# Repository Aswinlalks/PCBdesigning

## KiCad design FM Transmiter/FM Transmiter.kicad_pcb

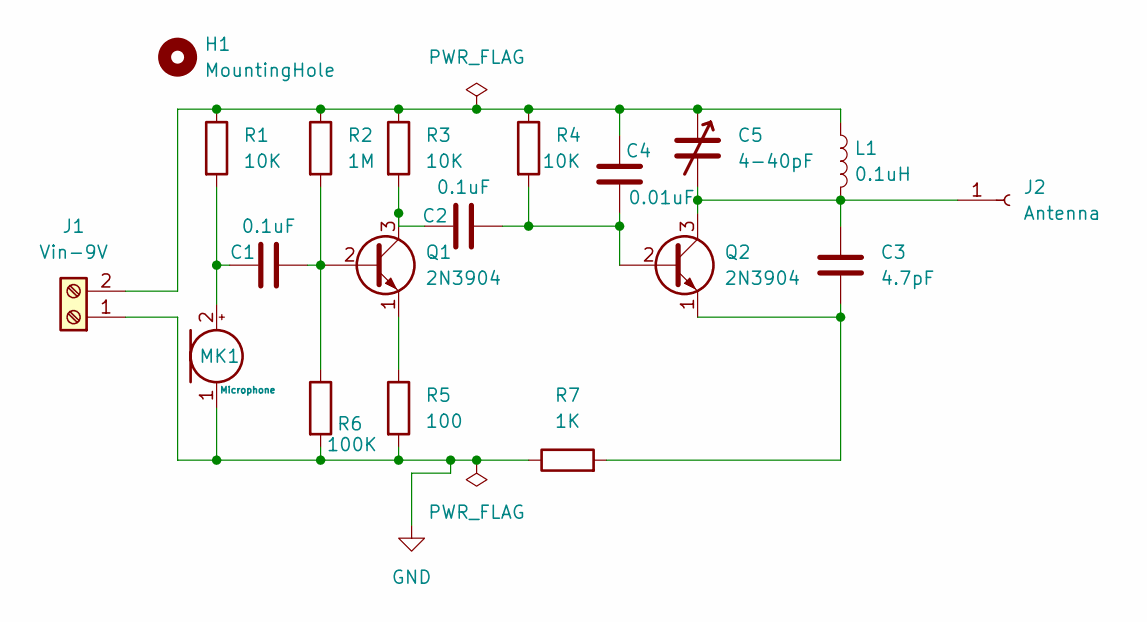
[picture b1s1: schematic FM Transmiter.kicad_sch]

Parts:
C1, C2: 0.1uF; C_Disc_D4.3mm_W1.9mm_P5.00mm
C3: 4.7pF; C_Disc_D4.3mm_W1.9mm_P5.00mm
C4: 0.01uF; C_Disc_D4.3mm_W1.9mm_P5.00mm
C5: 4-40pF; caps_trimmer
H1: MountingHole; MountingHole_2.2mm_M2
J1: Vin-9V; TerminalBlock_bornier-2_P5.08mm
J2: Antenna; TestPoint_THTPad_1.0x1.0mm_Drill0.5mm
L1: 0.1uH; L_Axial_L6.6mm_D2.7mm_P10.16mm_Horizontal_Vishay_IM-2
MK1: Microphone; Microphone electret
Q1, Q2: 2N3904; TO-92_Inline
R1, R3, R4: 10K; R_Axial_DIN0204_L3.6mm_D1.6mm_P7.62mm_Horizontal
R2: 1M; R_Axial_DIN0204_L3.6mm_D1.6mm_P7.62mm_Horizontal
R5: 100; R_Axial_DIN0204_L3.6mm_D1.6mm_P7.62mm_Horizontal
R6: 100K; R_Axial_DIN0204_L3.6mm_D1.6mm_P7.62mm_Horizontal
R7: 1K; R_Axial_DIN0204_L3.6mm_D1.6mm_P7.62mm_Horizontal

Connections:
GND: J1.1, MK1.1 (-), R5.2, R6.2, R7.1
unnamed: C4.1, C5.1, J1.2, L1.1, R1.1, R2.1, R3.1, R4.1
unnamed: C3.1, C5.2, J2.1, L1.2, Q2.3 (C)
unnamed: C1.1, MK1.2 (+), R1.2
unnamed: C1.2, Q1.2 (B), R2.2, R6.1
unnamed: C2.1, Q1.3 (C), R3.2
unnamed: Q1.1 (E), R5.1
unnamed: C2.2, C4.2, Q2.2 (B), R4.2
unnamed: C3.2, Q2.1 (E), R7.2

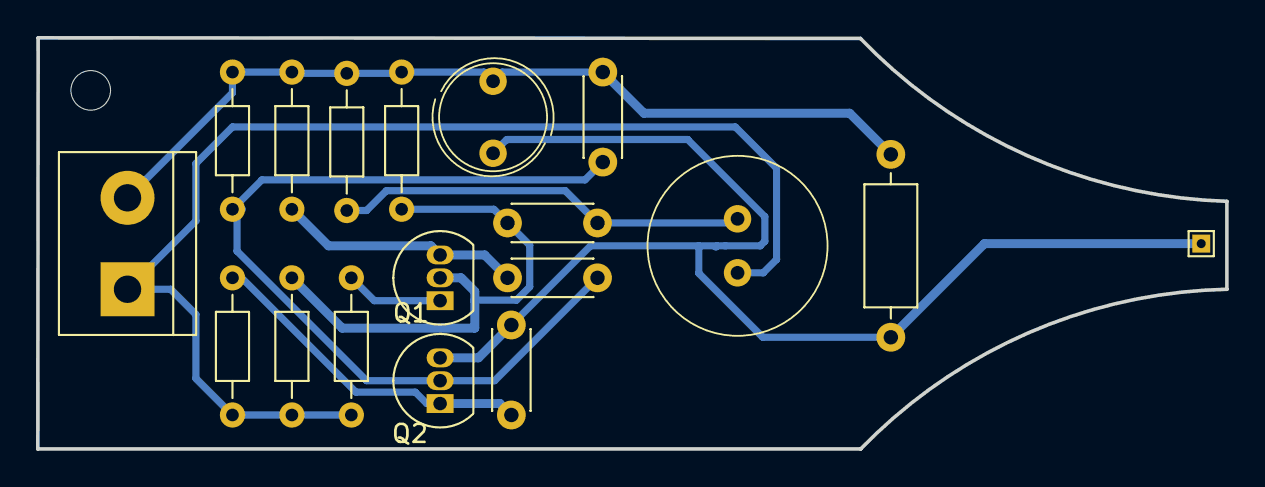
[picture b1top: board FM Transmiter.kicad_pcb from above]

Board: 2 copper layers, 66.1 x 22.8 mm, 19 parts (0 on the bottom side), 9 nets.

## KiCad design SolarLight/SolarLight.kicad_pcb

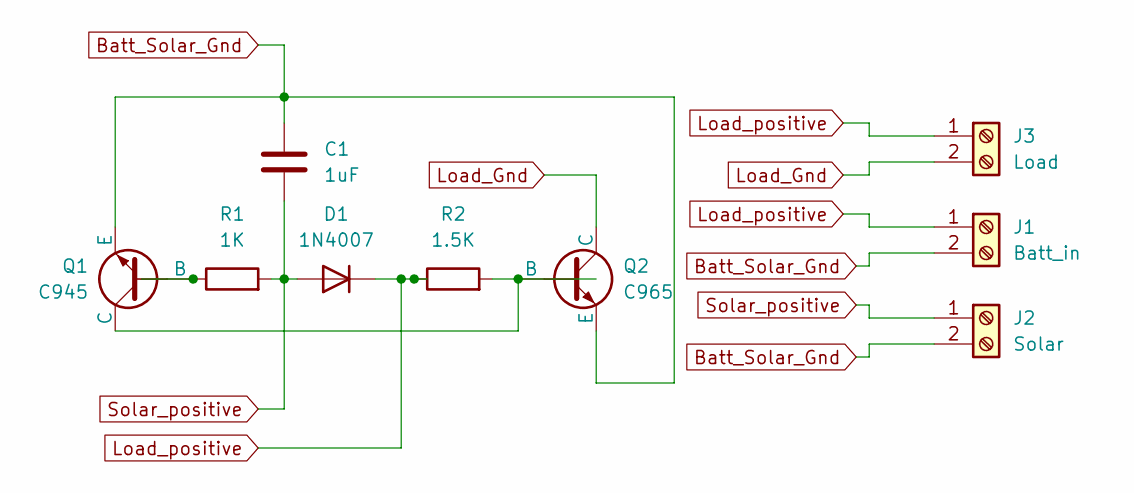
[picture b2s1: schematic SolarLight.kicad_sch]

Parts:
C1: 1uF; CP_Radial_D4.0mm_P2.00mm
D1: 1N4007; D_A-405_P7.62mm_Horizontal
J1: Batt_in; TerminalBlock_bornier-2_P5.08mm
J2: Solar; TerminalBlock_bornier-2_P5.08mm
J3: Load; TerminalBlock_bornier-2_P5.08mm
Q1: C945; TO-92L
Q2: C965; TO-92L
R1: 1K; R_Axial_DIN0204_L3.6mm_D1.6mm_P5.08mm_Horizontal
R2: 1.5K; R_Axial_DIN0204_L3.6mm_D1.6mm_P5.08mm_Horizontal

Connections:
Batt_Solar_Gnd: C1.2, J1.2, J2.2, Q1.3 (E), Q2.3 (E)
Load_Gnd: J3.2, Q2.1 (C)
Load_positive: D1.1 (K), J1.1, J3.1, R2.1
unnamed: Q1.2 (B), R1.1
unnamed: Q1.1 (C), Q2.2 (B), R2.2
Solar_positive: C1.1, D1.2 (A), J2.1, R1.2

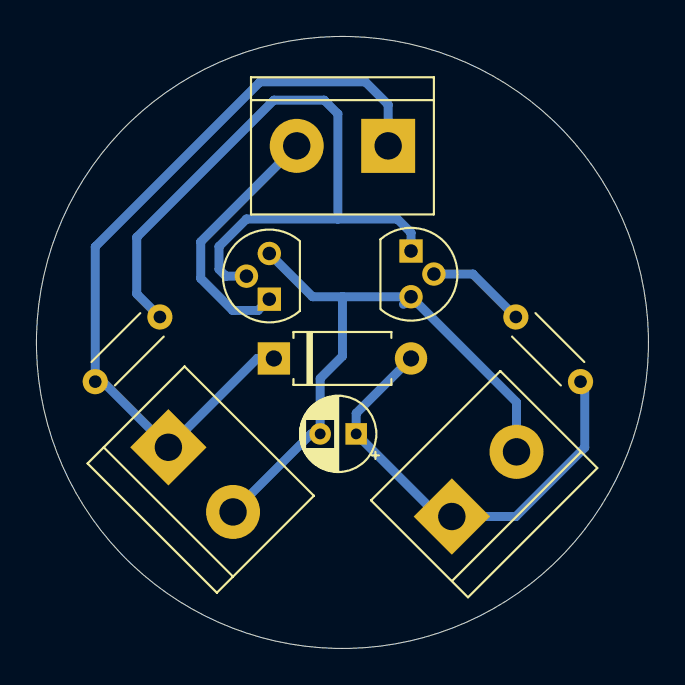
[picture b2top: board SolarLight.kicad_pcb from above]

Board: 2 copper layers, 34.0 x 34.0 mm, 9 parts (0 on the bottom side), 6 nets.

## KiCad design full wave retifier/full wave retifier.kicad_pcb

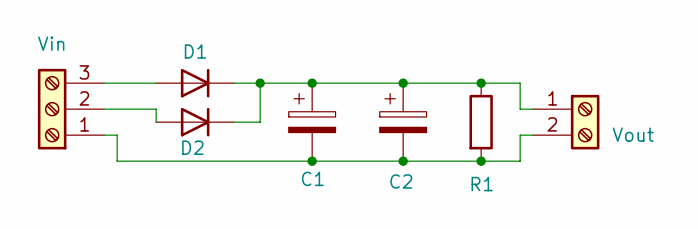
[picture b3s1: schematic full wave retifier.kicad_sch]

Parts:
C1, C2: C_Polarized; CP_Radial_D4.0mm_P2.00mm
D1, D2: D; D_5W_P12.70mm_Horizontal
J1: Vin; TerminalBlock_MaiXu_MX126-5.0-03P_1x03_P5.00mm
J2: Vout; TerminalBlock_MaiXu_MX126-5.0-02P_1x02_P5.00mm
R1: R; R_Axial_DIN0204_L3.6mm_D1.6mm_P5.08mm_Horizontal

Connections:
unnamed: D1.2 (A), J1.3
unnamed: C1.1, C2.1, D1.1 (K), D2.1 (K), J2.1, R1.1
unnamed: D2.2 (A), J1.2
unnamed: C1.2, C2.2, J1.1, J2.2, R1.2

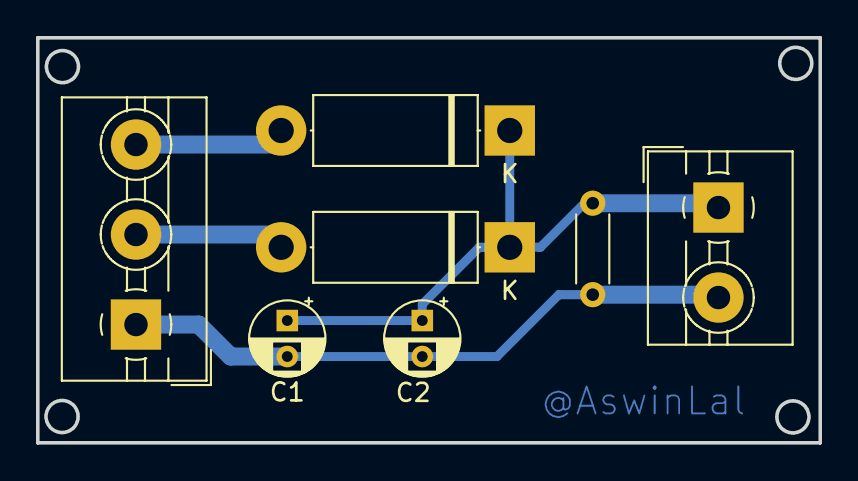
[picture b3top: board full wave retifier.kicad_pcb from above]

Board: 2 copper layers, 43.5 x 22.5 mm, 7 parts (0 on the bottom side), 4 nets.

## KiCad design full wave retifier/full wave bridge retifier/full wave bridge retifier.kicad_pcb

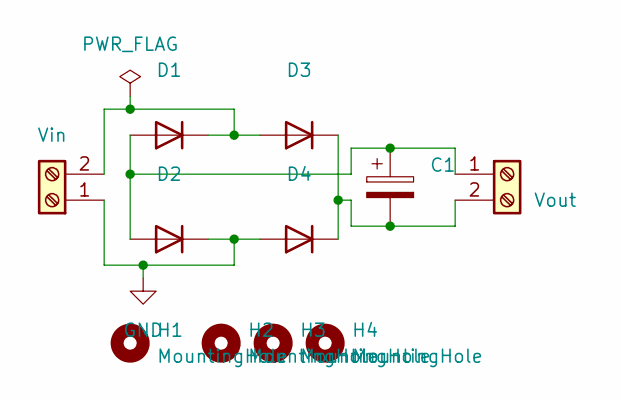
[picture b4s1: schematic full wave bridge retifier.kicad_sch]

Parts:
C1: C_Polarized; CP_Radial_D10.0mm_P7.50mm
D1, D2, D3, D4: D; D_5W_P12.70mm_Horizontal
H1, H2, H3, H4: MountingHole; MountingHole_2.1mm
J1: Vin; TerminalBlock_bornier-2_P5.08mm
J2: Vout; TerminalBlock_bornier-2_P5.08mm

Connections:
GND: D2.1 (K), D4.2 (A), J1.1
unnamed: C1.1, D1.2 (A), D2.2 (A), J2.1
unnamed: D1.1 (K), D3.2 (A), J1.2
unnamed: C1.2, D3.1 (K), D4.1 (K), J2.2

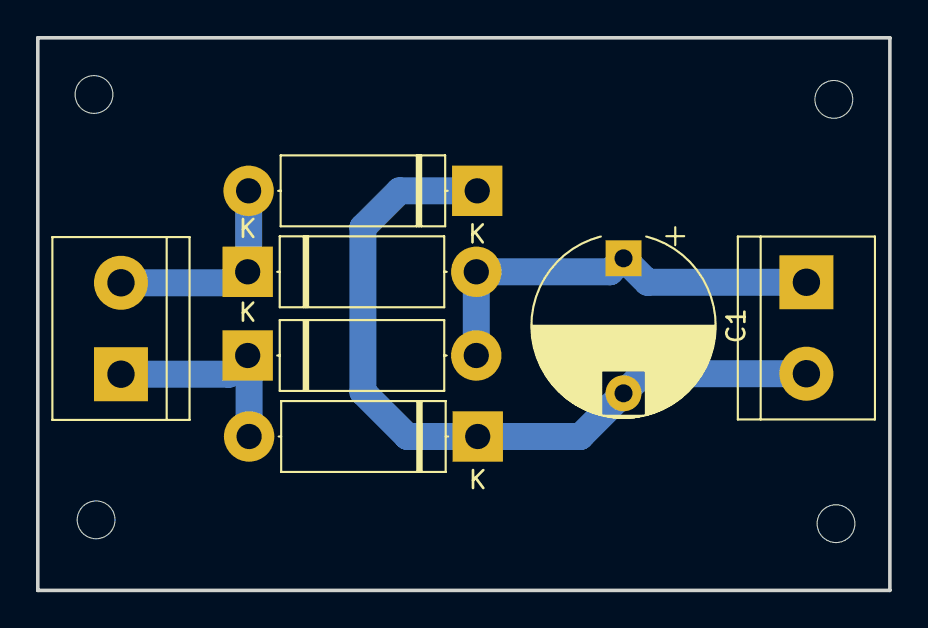
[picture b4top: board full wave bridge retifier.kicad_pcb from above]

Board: 2 copper layers, 47.3 x 30.7 mm, 11 parts (0 on the bottom side), 4 nets.

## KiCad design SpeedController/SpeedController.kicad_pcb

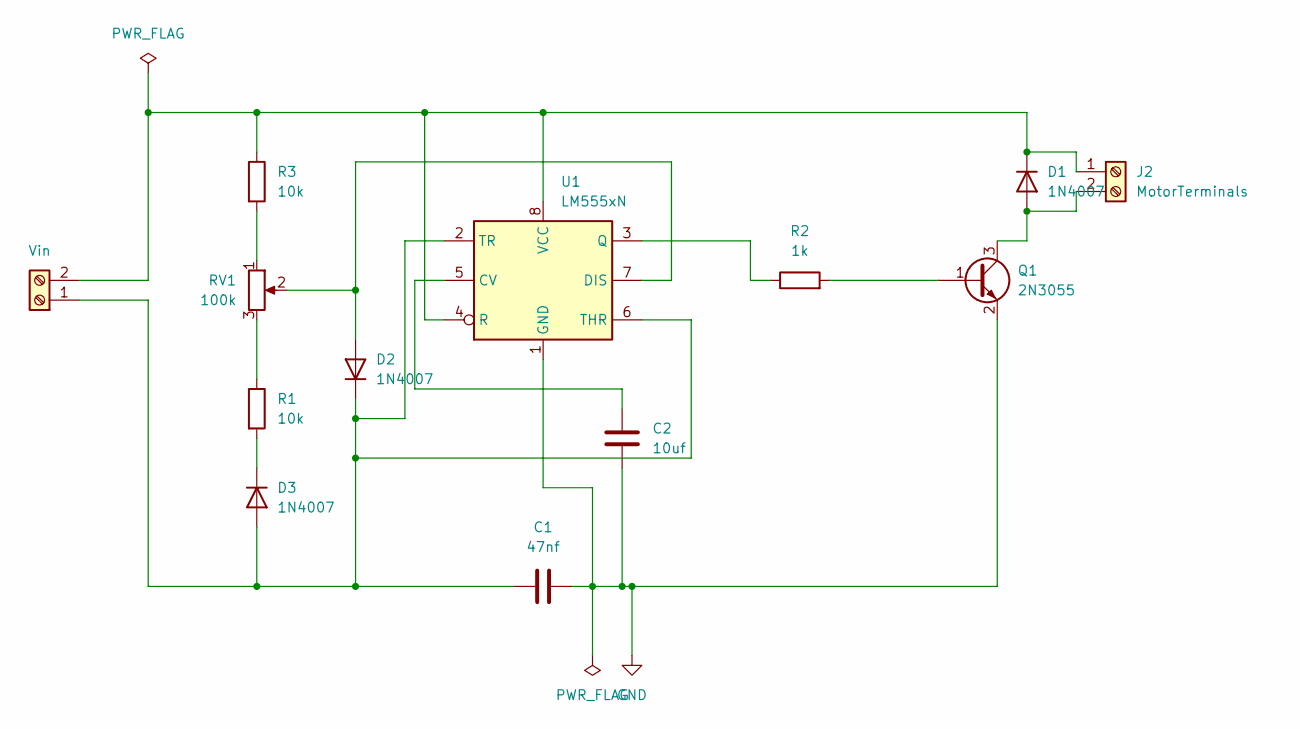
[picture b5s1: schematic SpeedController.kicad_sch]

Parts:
C1: 47nf; CP_Radial_D5.0mm_P2.00mm
C2: 10uf; CP_Radial_D5.0mm_P2.00mm
D1, D2, D3: 1N4007; D_5W_P12.70mm_Horizontal
J1: Vin; TerminalBlock_bornier-2_P5.08mm
J2: MotorTerminals; TerminalBlock_bornier-2_P5.08mm
Q1: 2N3055; TO-3
R1, R3: 10k; R_Axial_DIN0204_L3.6mm_D1.6mm_P5.08mm_Horizontal
R2: 1k; R_Axial_DIN0204_L3.6mm_D1.6mm_P5.08mm_Horizontal
RV1: 100k; Potentiometer_Alps_RK163_Single_Horizontal
U1: LM555xN; DIP-8_W7.62mm

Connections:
GND: C1.2, C2.2, Q1.2 (E), U1.1 (GND)
unnamed: D1.2 (A), J2.2, Q1.3 (C)
unnamed: D1.1 (K), J1.2, J2.1, R3.1, U1.4 (R), U1.8 (VCC)
unnamed: D2.2 (A), RV1.2, U1.7 (DIS)
unnamed: C1.1, D2.1 (K), D3.2 (A), J1.1, U1.2 (TR), U1.6 (THR)
unnamed: D3.1 (K), R1.2
unnamed: Q1.1 (B), R2.2
unnamed: R1.1, RV1.3
unnamed: R3.2, RV1.1
unnamed: C2.1, U1.5 (CV)
unnamed: R2.1, U1.3 (Q)

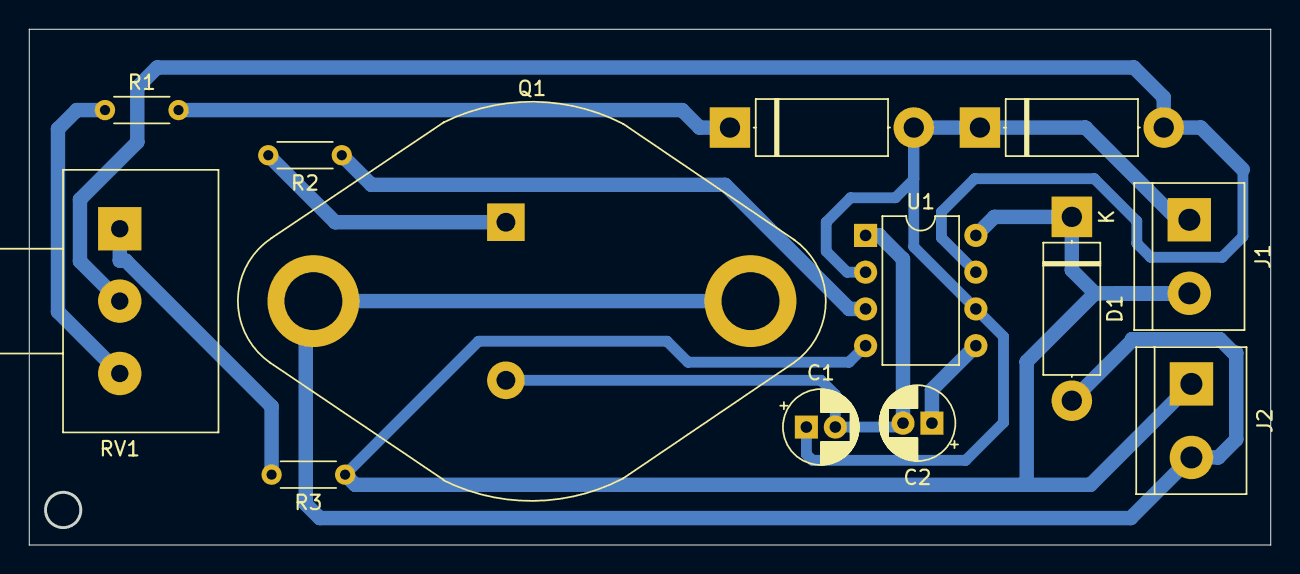
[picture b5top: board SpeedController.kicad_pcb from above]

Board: 2 copper layers, 85.6 x 35.5 mm, 13 parts (0 on the bottom side), 11 nets.

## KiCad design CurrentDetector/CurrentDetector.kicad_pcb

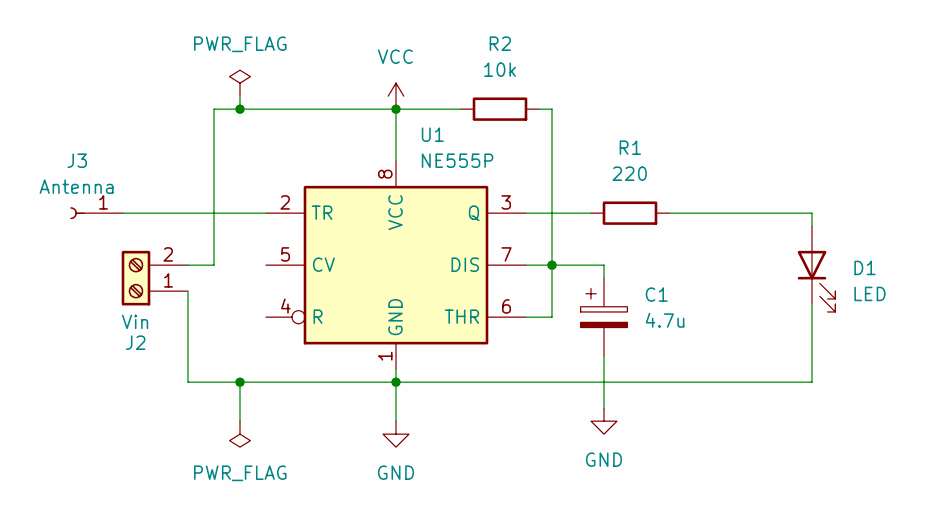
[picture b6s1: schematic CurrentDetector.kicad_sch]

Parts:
C1: 4.7u; CP_Radial_D5.0mm_P2.00mm
D1: LED; LED_D5.0mm
J2: Vin; TerminalBlock_bornier-2_P5.08mm
J3: Antenna; TestPoint_Keystone_5000-5004_Miniature
R1: 220; R_Axial_DIN0204_L3.6mm_D1.6mm_P5.08mm_Horizontal
R2: 10k; R_Axial_DIN0204_L3.6mm_D1.6mm_P5.08mm_Horizontal
U1: NE555P; DIP-8_W7.62mm

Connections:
GND: C1.2, D1.1 (K), J2.1, U1.1 (GND)
unnamed: D1.2 (A), R1.2
unnamed: J3.1, U1.2 (TR)
unnamed: C1.1, R2.2, U1.6 (THR), U1.7 (DIS)
unnamed: R1.1, U1.3 (Q)
VCC: J2.2, R2.1, U1.8 (VCC)

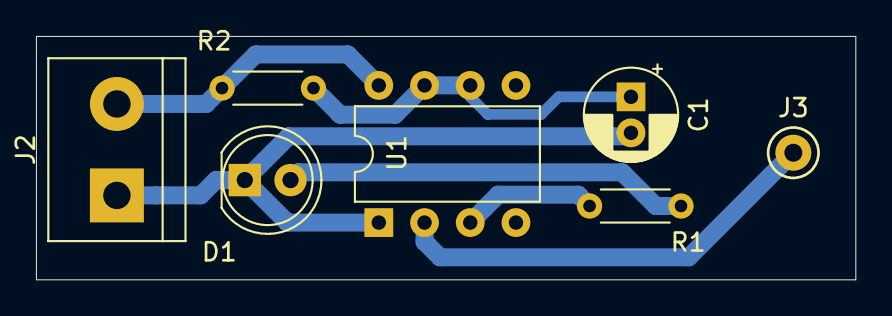
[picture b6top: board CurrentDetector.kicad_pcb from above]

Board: 2 copper layers, 45.5 x 13.5 mm, 7 parts (0 on the bottom side), 6 nets.

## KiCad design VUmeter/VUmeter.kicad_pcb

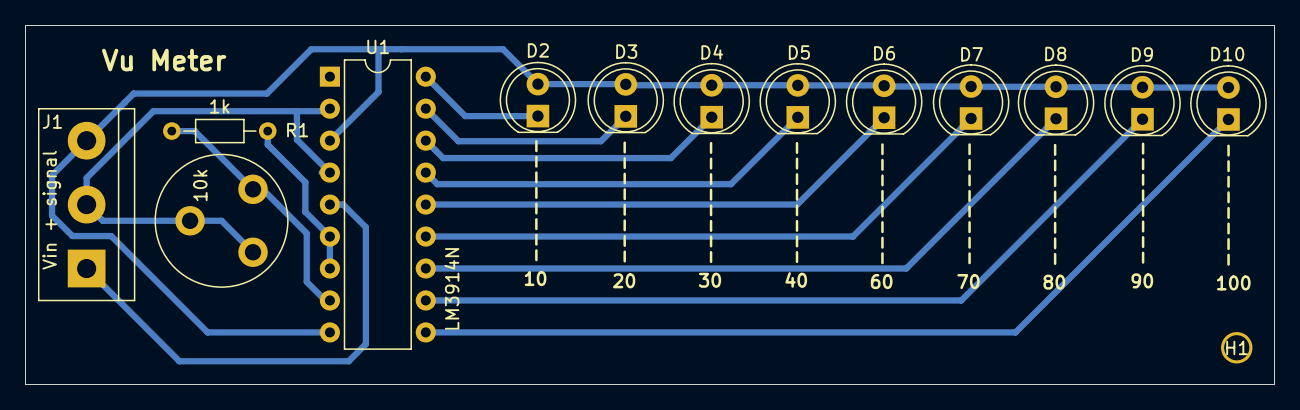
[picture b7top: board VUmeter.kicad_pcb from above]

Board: 2 copper layers, 99.3 x 28.5 mm, 14 parts (0 on the bottom side), 14 nets.

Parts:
D2: LED2; LED_D5.0mm
D3: LED3; LED_D5.0mm
D4: LED4; LED_D5.0mm
D5: LED5; LED_D5.0mm
D6: LED6; LED_D5.0mm
D7: LED7; LED_D5.0mm
D8: LED8; LED_D5.0mm
D9: LED9; LED_D5.0mm
D10: LED10; LED_D5.0mm
H1: MountingHole; MountingHole_2.5mm
J1: Vin + signal; TerminalBlock_bornier-3_P5.08mm
R1: 1k; R_Axial_DIN0204_L3.6mm_D1.6mm_P7.62mm_Horizontal
RV1: 10k; Potentiometer_Piher_PT-10-V05_Vertical
U1: LM3914N; DIP-18_W7.62mm

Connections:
GND: J1.2, RV1.2, RV1.3, U1.2 (V-), U1.4 (RLO)
unnamed: D2.1 (K), U1.18 (LED2)
unnamed: D3.1 (K), U1.17 (LED3)
unnamed: D4.1 (K), U1.16 (LED4)
unnamed: D5.1 (K), U1.15 (LED5)
unnamed: D6.1 (K), U1.14 (LED6)
unnamed: D7.1 (K), U1.13 (LED7)
unnamed: D8.1 (K), U1.12 (LED8)
unnamed: D9.1 (K), U1.11 (LED9)
unnamed: D2.2 (A), D3.2 (A), D4.2 (A), D5.2 (A), D6.2 (A), D7.2 (A), D8.2 (A), D9.2 (A), D10.2 (A), J1.3, U1.3 (V+), U1.9 (MODE)
unnamed: D10.1 (K), U1.10 (LED10)
unnamed: J1.1, U1.5 (SIG)
unnamed: R1.2, RV1.1, U1.8 (REFADJ)
unnamed: R1.1, U1.6 (RHI), U1.7 (REFOUT)
